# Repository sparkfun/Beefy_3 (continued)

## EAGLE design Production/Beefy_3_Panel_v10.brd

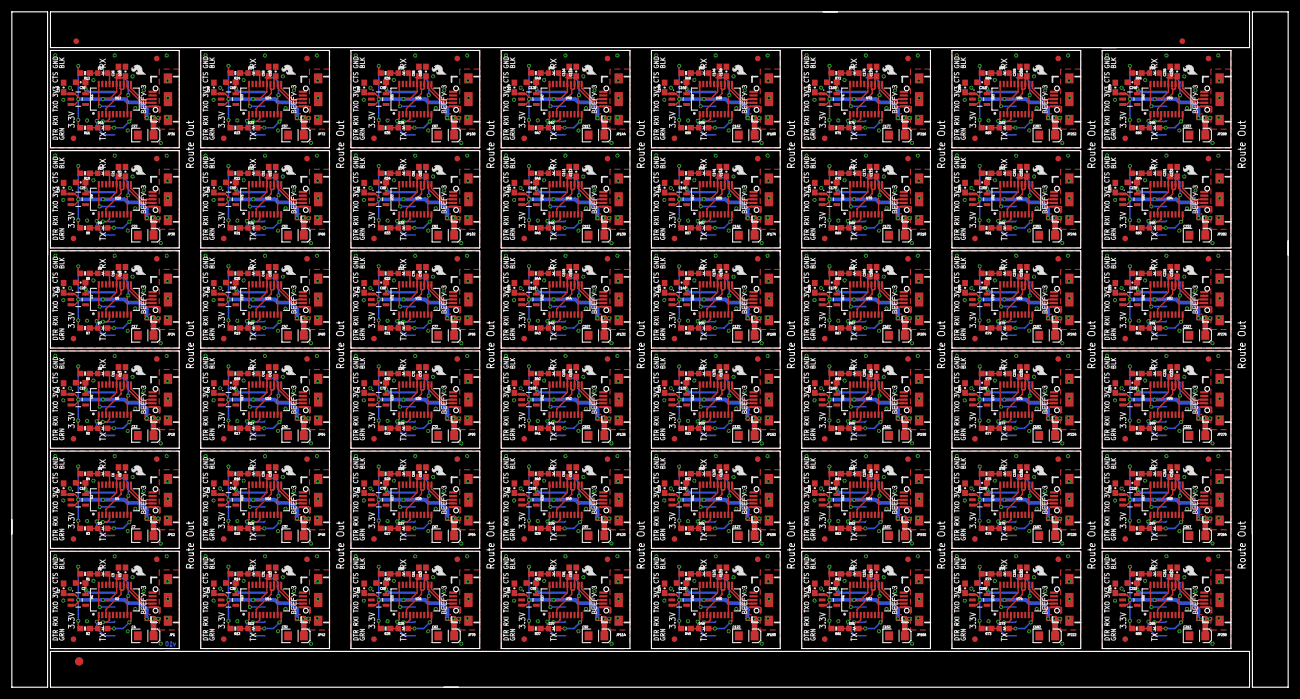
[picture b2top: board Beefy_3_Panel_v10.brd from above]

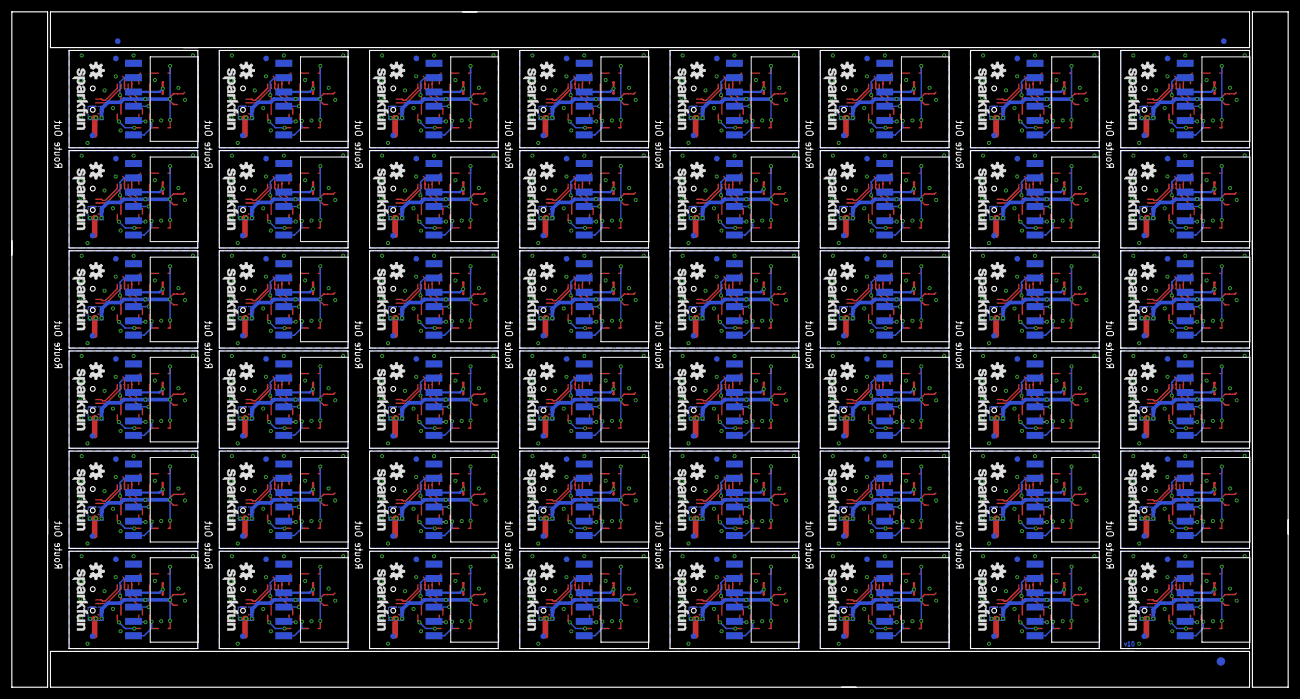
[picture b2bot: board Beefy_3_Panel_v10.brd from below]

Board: 2 copper layers, 226.6 x 119.9 mm, 966 parts (243 on the bottom side), 720 nets.

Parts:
C1, C2, C9, C10, C14, C15, C19, C20, C24, C25, C29, C30, C34, C35, C39, C40, C44, C45, C49, C50, C54, C55, C59, C60, C64, C65, C69, C70, C74, C75, C79, C80, C84, C85, C89, C90, C94, C95, C99, C100, C104, C105, C109, C110, C114, C115, C119, C120, C124, C125, C129, C130, C134, C135, C139, C140, C144, C145, C149, C150, C154, C155, C159, C160, C164, C165, C169, C170, C174, C175, C179, C180, C184, C185, C189, C190, C194, C195, C199, C200, C204, C205, C209, C210, C214, C215, C219, C220, C224, C225, C229, C230, C234, C235, C239, C240: 1.0uF; 0603-CAP
C3, C5, C6, C8, C11, C13, C16, C18, C21, C23, C26, C28, C31, C33, C36, C38, C41, C43, C46, C48, C51, C53, C56, C58, C61, C63, C66, C68, C71, C73, C76, C78, C81, C83, C86, C88, C91, C93, C96, C98, C101, C103, C106, C108, C111, C113, C116, C118, C121, C123, C126, C128, C131, C133, C136, C138, C141, C143, C146, C148, C151, C153, C156, C158, C161, C163, C166, C168, C171, C173, C176, C178, C181, C183, C186, C188, C191, C193, C196, C198, C201, C203, C206, C208, C211, C213, C216, C218, C221, C223, C226, C228, C231, C233, C236, C238: 0.1uF; 0603-CAP
C4, C7, C12, C17, C22, C27, C32, C37, C42, C47, C52, C57, C62, C67, C72, C77, C82, C87, C92, C97, C102, C107, C112, C117, C122, C127, C132, C137, C142, C147, C152, C157, C162, C167, C172, C177, C182, C187, C192, C197, C202, C207, C212, C217, C222, C227, C232, C237: 10uF; EIA3216
D1, D4, D6, D8, D10, D12, D14, D16, D18, D20, D22, D24, D26, D28, D30, D32, D34, D36, D38, D40, D42, D44, D46, D48, D50, D52, D54, D56, D58, D60, D62, D64, D66, D68, D70, D72, D74, D76, D78, D80, D82, D84, D86, D88, D90, D92, D94, D96: GREEN; LED-0603
D2, D3, D5, D7, D9, D11, D13, D15, D17, D19, D21, D23, D25, D27, D29, D31, D33, D35, D37, D39, D41, D43, D45, D47, D49, D51, D53, D55, D57, D59, D61, D63, D65, D67, D69, D71, D73, D75, D77, D79, D81, D83, D85, D87, D89, D91, D93, D95: RED; LED-0603
E$1, E$2: FIDUCIAL-1.5X3
E$3, E$4, E$7, E$8: FIDUCIAL-1X2
JP1, JP12, JP18, JP24, JP30, JP36, JP42, JP48, JP54, JP60, JP66, JP72, JP78, JP84, JP90, JP96, JP102, JP108, JP114, JP120, JP126, JP132, JP138, JP144, JP150, JP156, JP162, JP168, JP174, JP180, JP186, JP192, JP198, JP204, JP210, JP216, JP222, JP228, JP234, JP240, JP246, JP252, JP258, JP264, JP270, JP276, JP282, JP288: USB-B-MICRO-SMD_V03
JP2, JP7, JP13, JP19, JP25, JP31, JP37, JP43, JP49, JP55, JP61, JP67, JP73, JP79, JP85, JP91, JP97, JP103, JP109, JP115, JP121, JP127, JP133, JP139, JP145, JP151, JP157, JP163, JP169, JP175, JP181, JP187, JP193, JP199, JP205, JP211, JP217, JP223, JP229, JP235, JP241, JP247, JP253, JP259, JP265, JP271, JP277, JP283: 1X06-SMD-FEMALE-V2
JP3, JP4, JP5, JP6, JP8, JP9, JP10, JP11, JP14, JP15, JP16, JP17, JP20, JP21, JP22, JP23, JP26, JP27, JP28, JP29, JP32, JP33, JP34, JP35, JP38, JP39, JP40, JP41, JP44, JP45, JP46, JP47, JP50, JP51, JP52, JP53, JP56, JP57, JP58, JP59, JP62, JP63, JP64, JP65, JP68, JP69, JP70, JP71, JP74, JP75, JP76, JP77, JP80, JP81, JP82, JP83, JP86, JP87, JP88, JP89, JP92, JP93, JP94, JP95, JP98, JP99, JP100, JP101, JP104, JP105, JP106, JP107, JP110, JP111, JP112, JP113, JP116, JP117, JP118, JP119, JP122, JP123, JP124, JP125, JP128, JP129, JP130, JP131, JP134, JP135, JP136, JP137, JP140, JP141, JP142, JP143, JP146, JP147, JP148, JP149, JP152, JP153, JP154, JP155, JP158, JP159, JP160, JP161, JP164, JP165, JP166, JP167, JP170, JP171, JP172, JP173, JP176, JP177, JP178, JP179, JP182, JP183, JP184, JP185, JP188, JP189, JP190, JP191, JP194, JP195, JP196, JP197, JP200, JP201, JP202, JP203, JP206, JP207, JP208, JP209, JP212, JP213, JP214, JP215, JP218, JP219, JP220, JP221, JP224, JP225, JP226, JP227, JP230, JP231, JP232, JP233, JP236, JP237, JP238, JP239, JP242, JP243, JP244, JP245, JP248, JP249, JP250, JP251, JP254, JP255, JP256, JP257, JP260, JP261, JP262, JP263, JP266, JP267, JP268, JP269, JP272, JP273, JP274, JP275, JP278, JP279, JP280, JP281, JP284, JP285, JP286, JP287: FIDUCIAL1X2; FIDUCIAL-1X2
LOGO1, LOGO5, LOGO8, LOGO11, LOGO14, LOGO17, LOGO20, LOGO23, LOGO26, LOGO29, LOGO32, LOGO35, LOGO38, LOGO41, LOGO44, LOGO47, LOGO50, LOGO53, LOGO56, LOGO59, LOGO62, LOGO65, LOGO68, LOGO71, LOGO74, LOGO77, LOGO80, LOGO83, LOGO86, LOGO89, LOGO92, LOGO95, LOGO98, LOGO101, LOGO104, LOGO107, LOGO110, LOGO113, LOGO116, LOGO119, LOGO122, LOGO125, LOGO128, LOGO131, LOGO134, LOGO137, LOGO140, LOGO143: OSHW-LOGOS; OSHW-LOGO-S
LOGO2, LOGO4, LOGO7, LOGO10, LOGO13, LOGO16, LOGO19, LOGO22, LOGO25, LOGO28, LOGO31, LOGO34, LOGO37, LOGO40, LOGO43, LOGO46, LOGO49, LOGO52, LOGO55, LOGO58, LOGO61, LOGO64, LOGO67, LOGO70, LOGO73, LOGO76, LOGO79, LOGO82, LOGO85, LOGO88, LOGO91, LOGO94, LOGO97, LOGO100, LOGO103, LOGO106, LOGO109, LOGO112, LOGO115, LOGO118, LOGO121, LOGO124, LOGO127, LOGO130, LOGO133, LOGO136, LOGO139, LOGO142: SFE_LOGO_NAME.1_INCH; SFE_LOGO_NAME_.1
LOGO3, LOGO6, LOGO9, LOGO12, LOGO15, LOGO18, LOGO21, LOGO24, LOGO27, LOGO30, LOGO33, LOGO36, LOGO39, LOGO42, LOGO45, LOGO48, LOGO51, LOGO54, LOGO57, LOGO60, LOGO63, LOGO66, LOGO69, LOGO72, LOGO75, LOGO78, LOGO81, LOGO84, LOGO87, LOGO90, LOGO93, LOGO96, LOGO99, LOGO102, LOGO105, LOGO108, LOGO111, LOGO114, LOGO117, LOGO120, LOGO123, LOGO126, LOGO129, LOGO132, LOGO135, LOGO138, LOGO141, LOGO144: SFE_LOGO_FLAME.1_INCH; SFE_LOGO_FLAME_.1
R1, R2, R3, R4, R5, R6, R7, R8, R9, R10, R11, R12, R13, R14, R15, R16, R17, R18, R19, R20, R21, R22, R23, R24, R25, R26, R27, R28, R29, R30, R31, R32, R33, R34, R35, R36, R37, R38, R39, R40, R41, R42, R43, R44, R45, R46, R47, R48, R49, R50, R51, R52, R53, R54, R55, R56, R57, R58, R59, R60, R61, R62, R63, R64, R65, R66, R67, R68, R69, R70, R71, R72, R73, R74, R75, R76, R77, R78, R79, R80, R81, R82, R83, R84, R85, R86, R87, R88, R89, R90, R91, R92, R93, R94, R95, R96: 1K; 0603-RES
U1, U3, U5, U7, U9, U11, U13, U15, U17, U19, U21, U23, U25, U27, U29, U31, U33, U35, U37, U39, U41, U43, U45, U47, U49, U51, U53, U55, U57, U59, U61, U63, U65, U67, U69, U71, U73, U75, U77, U79, U81, U83, U85, U87, U89, U91, U93, U95: 3.3V; SOT23-5
U2, U4, U6, U8, U10, U12, U14, U16, U18, U20, U22, U24, U26, U28, U30, U32, U34, U36, U38, U40, U42, U44, U46, U48, U50, U52, U54, U56, U58, U60, U62, U64, U66, U68, U70, U72, U74, U76, U78, U80, U82, U84, U86, U88, U90, U92, U94, U96: FTS31XS-U; SSOP20_L

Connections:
3V1: C10.1, JP7.3, U3.5
3V2: C15.1, JP13.3, U5.5
3V3: C2.1, JP2.3, U1.5
3V3LC: C5.1, U2.3, U2.13, U2.14
3V3LC1: C8.1, U4.3, U4.13, U4.14
3V3LC2: C13.1, U6.3, U6.13, U6.14
3V3LC3: C18.1, U8.3, U8.13, U8.14
3V3LC4: C23.1, U10.3, U10.13, U10.14
3V3LC5: C28.1, U12.3, U12.13, U12.14
3V3LC6: C33.1, U14.3, U14.13, U14.14
3V3LC7: C38.1, U16.3, U16.13, U16.14
3V3LC8: C43.1, U18.3, U18.13, U18.14
3V3LC9: C48.1, U20.3, U20.13, U20.14
3V3LC10: C53.1, U22.3, U22.13, U22.14
3V3LC11: C58.1, U24.3, U24.13, U24.14
3V3LC12: C63.1, U26.3, U26.13, U26.14
3V3LC13: C68.1, U28.3, U28.13, U28.14
3V3LC14: C73.1, U30.3, U30.13, U30.14
3V3LC15: C78.1, U32.3, U32.13, U32.14
3V3LC16: C83.1, U34.3, U34.13, U34.14
3V3LC17: C88.1, U36.3, U36.13, U36.14
3V3LC18: C93.1, U38.3, U38.13, U38.14
3V3LC19: C98.1, U40.3, U40.13, U40.14
3V3LC20: C103.1, U42.3, U42.13, U42.14
3V3LC21: C108.1, U44.3, U44.13, U44.14
3V3LC22: C113.1, U46.3, U46.13, U46.14
3V3LC23: C118.1, U48.3, U48.13, U48.14
3V3LC24: C123.1, U50.3, U50.13, U50.14
3V3LC25: C128.1, U52.3, U52.13, U52.14
3V3LC26: C133.1, U54.3, U54.13, U54.14
3V3LC27: C138.1, U56.3, U56.13, U56.14
3V3LC28: C143.1, U58.3, U58.13, U58.14
3V3LC29: C148.1, U60.3, U60.13, U60.14
3V3LC30: C153.1, U62.3, U62.13, U62.14
3V3LC31: C158.1, U64.3, U64.13, U64.14
3V3LC32: C163.1, U66.3, U66.13, U66.14
3V3LC33: C168.1, U68.3, U68.13, U68.14
3V3LC34: C173.1, U70.3, U70.13, U70.14
3V3LC35: C178.1, U72.3, U72.13, U72.14
3V3LC36: C183.1, U74.3, U74.13, U74.14
3V3LC37: C188.1, U76.3, U76.13, U76.14
3V3LC38: C193.1, U78.3, U78.13, U78.14
3V3LC39: C198.1, U80.3, U80.13, U80.14
3V3LC40: C203.1, U82.3, U82.13, U82.14
3V3LC41: C208.1, U84.3, U84.13, U84.14
3V3LC42: C213.1, U86.3, U86.13, U86.14
3V3LC43: C218.1, U88.3, U88.13, U88.14
3V3LC44: C223.1, U90.3, U90.13, U90.14
3V3LC45: C228.1, U92.3, U92.13, U92.14
3V3LC46: C233.1, U94.3, U94.13, U94.14
3V3LC47: C238.1, U96.3, U96.13, U96.14
3V4: C20.1, JP19.3, U7.5
3V5: C25.1, JP25.3, U9.5
3V6: C30.1, JP31.3, U11.5
3V7: C35.1, JP37.3, U13.5
3V8: C40.1, JP43.3, U15.5
3V9: C45.1, JP49.3, U17.5
3V10: C50.1, JP55.3, U19.5
3V11: C55.1, JP61.3, U21.5
3V12: C60.1, JP67.3, U23.5
3V13: C65.1, JP73.3, U25.5
3V14: C70.1, JP79.3, U27.5
3V15: C75.1, JP85.3, U29.5
3V16: C80.1, JP91.3, U31.5
3V17: C85.1, JP97.3, U33.5
3V18: C90.1, JP103.3, U35.5
3V19: C95.1, JP109.3, U37.5
3V20: C100.1, JP115.3, U39.5
3V21: C105.1, JP121.3, U41.5
3V22: C110.1, JP127.3, U43.5
3V23: C115.1, JP133.3, U45.5
3V24: C120.1, JP139.3, U47.5
3V25: C125.1, JP145.3, U49.5
3V26: C130.1, JP151.3, U51.5
3V27: C135.1, JP157.3, U53.5
3V28: C140.1, JP163.3, U55.5
3V29: C145.1, JP169.3, U57.5
3V30: C150.1, JP175.3, U59.5
3V31: C155.1, JP181.3, U61.5
3V32: C160.1, JP187.3, U63.5
3V33: C165.1, JP193.3, U65.5
3V34: C170.1, JP199.3, U67.5
3V35: C175.1, JP205.3, U69.5
3V36: C180.1, JP211.3, U71.5
3V37: C185.1, JP217.3, U73.5
3V38: C190.1, JP223.3, U75.5
3V39: C195.1, JP229.3, U77.5
3V40: C200.1, JP235.3, U79.5
3V41: C205.1, JP241.3, U81.5
3V42: C210.1, JP247.3, U83.5
3V43: C215.1, JP253.3, U85.5
3V44: C220.1, JP259.3, U87.5
3V45: C225.1, JP265.3, U89.5
3V46: C230.1, JP271.3, U91.5
3V47: C235.1, JP277.3, U93.5
3V48: C240.1, JP283.3, U95.5
5V: C1.1, C3.1, C4.A, JP1.VBUS1, R1.2, R2.2, U1.1, U1.3, U2.15
5V1: C6.1, C7.A, C9.1, JP12.VBUS1, R3.2, R4.2, U3.1, U3.3, U4.15
5V2: C11.1, C12.A, C14.1, JP18.VBUS1, R5.2, R6.2, U5.1, U5.3, U6.15
5V3: C16.1, C17.A, C19.1, JP24.VBUS1, R7.2, R8.2, U7.1, U7.3, U8.15
5V4: C21.1, C22.A, C24.1, JP30.VBUS1, R9.2, R10.2, U9.1, U9.3, U10.15
5V5: C26.1, C27.A, C29.1, JP36.VBUS1, R11.2, R12.2, U11.1, U11.3, U12.15
5V6: C31.1, C32.A, C34.1, JP42.VBUS1, R13.2, R14.2, U13.1, U13.3, U14.15
5V7: C36.1, C37.A, C39.1, JP48.VBUS1, R15.2, R16.2, U15.1, U15.3, U16.15
5V8: C41.1, C42.A, C44.1, JP54.VBUS1, R17.2, R18.2, U17.1, U17.3, U18.15
5V9: C46.1, C47.A, C49.1, JP60.VBUS1, R19.2, R20.2, U19.1, U19.3, U20.15
5V10: C51.1, C52.A, C54.1, JP66.VBUS1, R21.2, R22.2, U21.1, U21.3, U22.15
5V11: C56.1, C57.A, C59.1, JP72.VBUS1, R23.2, R24.2, U23.1, U23.3, U24.15
5V12: C61.1, C62.A, C64.1, JP78.VBUS1, R25.2, R26.2, U25.1, U25.3, U26.15
5V13: C66.1, C67.A, C69.1, JP84.VBUS1, R27.2, R28.2, U27.1, U27.3, U28.15
5V14: C71.1, C72.A, C74.1, JP90.VBUS1, R29.2, R30.2, U29.1, U29.3, U30.15
5V15: C76.1, C77.A, C79.1, JP96.VBUS1, R31.2, R32.2, U31.1, U31.3, U32.15
5V16: C81.1, C82.A, C84.1, JP102.VBUS1, R33.2, R34.2, U33.1, U33.3, U34.15
5V17: C86.1, C87.A, C89.1, JP108.VBUS1, R35.2, R36.2, U35.1, U35.3, U36.15
5V18: C91.1, C92.A, C94.1, JP114.VBUS1, R37.2, R38.2, U37.1, U37.3, U38.15
5V19: C96.1, C97.A, C99.1, JP120.VBUS1, R39.2, R40.2, U39.1, U39.3, U40.15
5V20: C101.1, C102.A, C104.1, JP126.VBUS1, R41.2, R42.2, U41.1, U41.3, U42.15
5V21: C106.1, C107.A, C109.1, JP132.VBUS1, R43.2, R44.2, U43.1, U43.3, U44.15
5V22: C111.1, C112.A, C114.1, JP138.VBUS1, R45.2, R46.2, U45.1, U45.3, U46.15
5V23: C116.1, C117.A, C119.1, JP144.VBUS1, R47.2, R48.2, U47.1, U47.3, U48.15
5V24: C121.1, C122.A, C124.1, JP150.VBUS1, R49.2, R50.2, U49.1, U49.3, U50.15
5V25: C126.1, C127.A, C129.1, JP156.VBUS1, R51.2, R52.2, U51.1, U51.3, U52.15
5V26: C131.1, C132.A, C134.1, JP162.VBUS1, R53.2, R54.2, U53.1, U53.3, U54.15
5V27: C136.1, C137.A, C139.1, JP168.VBUS1, R55.2, R56.2, U55.1, U55.3, U56.15
5V28: C141.1, C142.A, C144.1, JP174.VBUS1, R57.2, R58.2, U57.1, U57.3, U58.15
5V29: C146.1, C147.A, C149.1, JP180.VBUS1, R59.2, R60.2, U59.1, U59.3, U60.15
5V30: C151.1, C152.A, C154.1, JP186.VBUS1, R61.2, R62.2, U61.1, U61.3, U62.15
5V31: C156.1, C157.A, C159.1, JP192.VBUS1, R63.2, R64.2, U63.1, U63.3, U64.15
5V32: C161.1, C162.A, C164.1, JP198.VBUS1, R65.2, R66.2, U65.1, U65.3, U66.15
5V33: C166.1, C167.A, C169.1, JP204.VBUS1, R67.2, R68.2, U67.1, U67.3, U68.15
5V34: C171.1, C172.A, C174.1, JP210.VBUS1, R69.2, R70.2, U69.1, U69.3, U70.15
5V35: C176.1, C177.A, C179.1, JP216.VBUS1, R71.2, R72.2, U71.1, U71.3, U72.15
5V36: C181.1, C182.A, C184.1, JP222.VBUS1, R73.2, R74.2, U73.1, U73.3, U74.15
5V37: C186.1, C187.A, C189.1, JP228.VBUS1, R75.2, R76.2, U75.1, U75.3, U76.15
5V38: C191.1, C192.A, C194.1, JP234.VBUS1, R77.2, R78.2, U77.1, U77.3, U78.15
5V39: C196.1, C197.A, C199.1, JP240.VBUS1, R79.2, R80.2, U79.1, U79.3, U80.15
5V40: C201.1, C202.A, C204.1, JP246.VBUS1, R81.2, R82.2, U81.1, U81.3, U82.15
5V41: C206.1, C207.A, C209.1, JP252.VBUS1, R83.2, R84.2, U83.1, U83.3, U84.15
5V42: C211.1, C212.A, C214.1, JP258.VBUS1, R85.2, R86.2, U85.1, U85.3, U86.15
5V43: C216.1, C217.A, C219.1, JP264.VBUS1, R87.2, R88.2, U87.1, U87.3, U88.15
5V44: C221.1, C222.A, C224.1, JP270.VBUS1, R89.2, R90.2, U89.1, U89.3, U90.15
5V45: C226.1, C227.A, C229.1, JP276.VBUS1, R91.2, R92.2, U91.1, U91.3, U92.15
5V46: C231.1, C232.A, C234.1, JP282.VBUS1, R93.2, R94.2, U93.1, U93.3, U94.15
5V47: C236.1, C237.A, C239.1, JP288.VBUS1, R95.2, R96.2, U95.1, U95.3, U96.15
!CTS: JP2.2, U2.9
!CTS1: JP7.2, U4.9
!CTS2: JP13.2, U6.9
!CTS3: JP19.2, U8.9
!CTS4: JP25.2, U10.9
!CTS5: JP31.2, U12.9
!CTS6: JP37.2, U14.9
!CTS7: JP43.2, U16.9
!CTS8: JP49.2, U18.9
!CTS9: JP55.2, U20.9
!CTS10: JP61.2, U22.9
!CTS11: JP67.2, U24.9
!CTS12: JP73.2, U26.9
!CTS13: JP79.2, U28.9
!CTS14: JP85.2, U30.9
!CTS15: JP91.2, U32.9
!CTS16: JP97.2, U34.9
!CTS17: JP103.2, U36.9
!CTS18: JP109.2, U38.9
!CTS19: JP115.2, U40.9
!CTS20: JP121.2, U42.9
!CTS21: JP127.2, U44.9
!CTS22: JP133.2, U46.9
!CTS23: JP139.2, U48.9
!CTS24: JP145.2, U50.9
!CTS25: JP151.2, U52.9
!CTS26: JP157.2, U54.9
!CTS27: JP163.2, U56.9
!CTS28: JP169.2, U58.9
!CTS29: JP175.2, U60.9
!CTS30: JP181.2, U62.9
!CTS31: JP187.2, U64.9
!CTS32: JP193.2, U66.9
!CTS33: JP199.2, U68.9
!CTS34: JP205.2, U70.9
!CTS35: JP211.2, U72.9
!CTS36: JP217.2, U74.9
!CTS37: JP223.2, U76.9
!CTS38: JP229.2, U78.9
!CTS39: JP235.2, U80.9
!CTS40: JP241.2, U82.9
!CTS41: JP247.2, U84.9
!CTS42: JP253.2, U86.9
!CTS43: JP259.2, U88.9
!CTS44: JP265.2, U90.9
!CTS45: JP271.2, U92.9
!CTS46: JP277.2, U94.9
!CTS47: JP283.2, U96.9
!DTR: JP2.6, U2.1
!DTR1: JP7.6, U4.1
!DTR2: JP13.6, U6.1
!DTR3: JP19.6, U8.1
!DTR4: JP25.6, U10.1
!DTR5: JP31.6, U12.1
!DTR6: JP37.6, U14.1
!DTR7: JP43.6, U16.1
!DTR8: JP49.6, U18.1
!DTR9: JP55.6, U20.1
!DTR10: JP61.6, U22.1
!DTR11: JP67.6, U24.1
!DTR12: JP73.6, U26.1
!DTR13: JP79.6, U28.1
!DTR14: JP85.6, U30.1
!DTR15: JP91.6, U32.1
!DTR16: JP97.6, U34.1
!DTR17: JP103.6, U36.1
!DTR18: JP109.6, U38.1
!DTR19: JP115.6, U40.1
!DTR20: JP121.6, U42.1
!DTR21: JP127.6, U44.1
!DTR22: JP133.6, U46.1
!DTR23: JP139.6, U48.1
!DTR24: JP145.6, U50.1
!DTR25: JP151.6, U52.1
!DTR26: JP157.6, U54.1
!DTR27: JP163.6, U56.1
!DTR28: JP169.6, U58.1
!DTR29: JP175.6, U60.1
!DTR30: JP181.6, U62.1
!DTR31: JP187.6, U64.1
!DTR32: JP193.6, U66.1
!DTR33: JP199.6, U68.1
!DTR34: JP205.6, U70.1
!DTR35: JP211.6, U72.1
!DTR36: JP217.6, U74.1
!DTR37: JP223.6, U76.1
!DTR38: JP229.6, U78.1
!DTR39: JP235.6, U80.1
!DTR40: JP241.6, U82.1
!DTR41: JP247.6, U84.1
!DTR42: JP253.6, U86.1
!DTR43: JP259.6, U88.1
!DTR44: JP265.6, U90.1
!DTR45: JP271.6, U92.1
!DTR46: JP277.6, U94.1
!DTR47: JP283.6, U96.1
GND: C1.2, C2.2, C3.2, C4.C, C5.2, JP1.GND1, JP2.1, U1.2, U2.6, U2.16
GND1: C6.2, C7.C, C8.2, C9.2, C10.2, JP7.1, JP12.GND1, U3.2, U4.6, U4.16
GND2: C11.2, C12.C, C13.2, C14.2, C15.2, JP13.1, JP18.GND1, U5.2, U6.6, U6.16
GND3: C16.2, C17.C, C18.2, C19.2, C20.2, JP19.1, JP24.GND1, U7.2, U8.6, U8.16
GND4: C21.2, C22.C, C23.2, C24.2, C25.2, JP25.1, JP30.GND1, U9.2, U10.6, U10.16
GND5: C26.2, C27.C, C28.2, C29.2, C30.2, JP31.1, JP36.GND1, U11.2, U12.6, U12.16
GND6: C31.2, C32.C, C33.2, C34.2, C35.2, JP37.1, JP42.GND1, U13.2, U14.6, U14.16
GND7: C36.2, C37.C, C38.2, C39.2, C40.2, JP43.1, JP48.GND1, U15.2, U16.6, U16.16
GND8: C41.2, C42.C, C43.2, C44.2, C45.2, JP49.1, JP54.GND1, U17.2, U18.6, U18.16
GND9: C46.2, C47.C, C48.2, C49.2, C50.2, JP55.1, JP60.GND1, U19.2, U20.6, U20.16
GND10: C51.2, C52.C, C53.2, C54.2, C55.2, JP61.1, JP66.GND1, U21.2, U22.6, U22.16
GND11: C56.2, C57.C, C58.2, C59.2, C60.2, JP67.1, JP72.GND1, U23.2, U24.6, U24.16
GND12: C61.2, C62.C, C63.2, C64.2, C65.2, JP73.1, JP78.GND1, U25.2, U26.6, U26.16
GND13: C66.2, C67.C, C68.2, C69.2, C70.2, JP79.1, JP84.GND1, U27.2, U28.6, U28.16
GND14: C71.2, C72.C, C73.2, C74.2, C75.2, JP85.1, JP90.GND1, U29.2, U30.6, U30.16
GND15: C76.2, C77.C, C78.2, C79.2, C80.2, JP91.1, JP96.GND1, U31.2, U32.6, U32.16
GND16: C81.2, C82.C, C83.2, C84.2, C85.2, JP97.1, JP102.GND1, U33.2, U34.6, U34.16
GND17: C86.2, C87.C, C88.2, C89.2, C90.2, JP103.1, JP108.GND1, U35.2, U36.6, U36.16
GND18: C91.2, C92.C, C93.2, C94.2, C95.2, JP109.1, JP114.GND1, U37.2, U38.6, U38.16
GND19: C96.2, C97.C, C98.2, C99.2, C100.2, JP115.1, JP120.GND1, U39.2, U40.6, U40.16
GND20: C101.2, C102.C, C103.2, C104.2, C105.2, JP121.1, JP126.GND1, U41.2, U42.6, U42.16
GND21: C106.2, C107.C, C108.2, C109.2, C110.2, JP127.1, JP132.GND1, U43.2, U44.6, U44.16
GND22: C111.2, C112.C, C113.2, C114.2, C115.2, JP133.1, JP138.GND1, U45.2, U46.6, U46.16
GND23: C116.2, C117.C, C118.2, C119.2, C120.2, JP139.1, JP144.GND1, U47.2, U48.6, U48.16
GND24: C121.2, C122.C, C123.2, C124.2, C125.2, JP145.1, JP150.GND1, U49.2, U50.6, U50.16
GND25: C126.2, C127.C, C128.2, C129.2, C130.2, JP151.1, JP156.GND1, U51.2, U52.6, U52.16
GND26: C131.2, C132.C, C133.2, C134.2, C135.2, JP157.1, JP162.GND1, U53.2, U54.6, U54.16
GND27: C136.2, C137.C, C138.2, C139.2, C140.2, JP163.1, JP168.GND1, U55.2, U56.6, U56.16
GND28: C141.2, C142.C, C143.2, C144.2, C145.2, JP169.1, JP174.GND1, U57.2, U58.6, U58.16
GND29: C146.2, C147.C, C148.2, C149.2, C150.2, JP175.1, JP180.GND1, U59.2, U60.6, U60.16
GND30: C151.2, C152.C, C153.2, C154.2, C155.2, JP181.1, JP186.GND1, U61.2, U62.6, U62.16
GND31: C156.2, C157.C, C158.2, C159.2, C160.2, JP187.1, JP192.GND1, U63.2, U64.6, U64.16
GND32: C161.2, C162.C, C163.2, C164.2, C165.2, JP193.1, JP198.GND1, U65.2, U66.6, U66.16
GND33: C166.2, C167.C, C168.2, C169.2, C170.2, JP199.1, JP204.GND1, U67.2, U68.6, U68.16
GND34: C171.2, C172.C, C173.2, C174.2, C175.2, JP205.1, JP210.GND1, U69.2, U70.6, U70.16
GND35: C176.2, C177.C, C178.2, C179.2, C180.2, JP211.1, JP216.GND1, U71.2, U72.6, U72.16
GND36: C181.2, C182.C, C183.2, C184.2, C185.2, JP217.1, JP222.GND1, U73.2, U74.6, U74.16
GND37: C186.2, C187.C, C188.2, C189.2, C190.2, JP223.1, JP228.GND1, U75.2, U76.6, U76.16
GND38: C191.2, C192.C, C193.2, C194.2, C195.2, JP229.1, JP234.GND1, U77.2, U78.6, U78.16
GND39: C196.2, C197.C, C198.2, C199.2, C200.2, JP235.1, JP240.GND1, U79.2, U80.6, U80.16
GND40: C201.2, C202.C, C203.2, C204.2, C205.2, JP241.1, JP246.GND1, U81.2, U82.6, U82.16
GND41: C206.2, C207.C, C208.2, C209.2, C210.2, JP247.1, JP252.GND1, U83.2, U84.6, U84.16
GND42: C211.2, C212.C, C213.2, C214.2, C215.2, JP253.1, JP258.GND1, U85.2, U86.6, U86.16
GND43: C216.2, C217.C, C218.2, C219.2, C220.2, JP259.1, JP264.GND1, U87.2, U88.6, U88.16
GND44: C221.2, C222.C, C223.2, C224.2, C225.2, JP265.1, JP270.GND1, U89.2, U90.6, U90.16
GND45: C226.2, C227.C, C228.2, C229.2, C230.2, JP271.1, JP276.GND1, U91.2, U92.6, U92.16
GND46: C231.2, C232.C, C233.2, C234.2, C235.2, JP277.1, JP282.GND1, U93.2, U94.6, U94.16
GND47: C236.2, C237.C, C238.2, C239.2, C240.2, JP283.1, JP288.GND1, U95.2, U96.6, U96.16
unnamed: D2.A, R2.1
unnamed: D1.A, R1.1
unnamed: D3.A, R3.1
unnamed: D4.A, R4.1
unnamed: D5.A, R5.1
unnamed: D6.A, R6.1
unnamed: D7.A, R7.1
unnamed: D8.A, R8.1
unnamed: D9.A, R9.1
unnamed: D10.A, R10.1
unnamed: D11.A, R11.1
unnamed: D12.A, R12.1
unnamed: D13.A, R13.1
unnamed: D14.A, R14.1
unnamed: D15.A, R15.1
unnamed: D16.A, R16.1
unnamed: D17.A, R17.1
unnamed: D18.A, R18.1
unnamed: D19.A, R19.1
unnamed: D20.A, R20.1
unnamed: D21.A, R21.1
unnamed: D22.A, R22.1
unnamed: D23.A, R23.1
unnamed: D24.A, R24.1
unnamed: D25.A, R25.1
unnamed: D26.A, R26.1
unnamed: D27.A, R27.1
unnamed: D28.A, R28.1
unnamed: D29.A, R29.1
unnamed: D30.A, R30.1
unnamed: D31.A, R31.1
unnamed: D32.A, R32.1
unnamed: D33.A, R33.1
unnamed: D34.A, R34.1
unnamed: D35.A, R35.1
unnamed: D36.A, R36.1
unnamed: D37.A, R37.1
unnamed: D38.A, R38.1
unnamed: D39.A, R39.1
unnamed: D40.A, R40.1
unnamed: D41.A, R41.1
unnamed: D42.A, R42.1
unnamed: D43.A, R43.1
unnamed: D44.A, R44.1
unnamed: D45.A, R45.1
unnamed: D46.A, R46.1
unnamed: D47.A, R47.1
unnamed: D48.A, R48.1
unnamed: D49.A, R49.1
unnamed: D50.A, R50.1
unnamed: D51.A, R51.1
unnamed: D52.A, R52.1
unnamed: D53.A, R53.1
unnamed: D54.A, R54.1
unnamed: D55.A, R55.1
unnamed: D56.A, R56.1
unnamed: D57.A, R57.1
unnamed: D58.A, R58.1
unnamed: D59.A, R59.1
unnamed: D60.A, R60.1
unnamed: D61.A, R61.1
unnamed: D62.A, R62.1
unnamed: D63.A, R63.1
unnamed: D64.A, R64.1
unnamed: D65.A, R65.1
unnamed: D66.A, R66.1
unnamed: D67.A, R67.1
unnamed: D68.A, R68.1
unnamed: D69.A, R69.1
unnamed: D70.A, R70.1
unnamed: D71.A, R71.1
unnamed: D72.A, R72.1
unnamed: D73.A, R73.1
unnamed: D74.A, R74.1
unnamed: D75.A, R75.1
unnamed: D76.A, R76.1
unnamed: D77.A, R77.1
unnamed: D78.A, R78.1
unnamed: D79.A, R79.1
unnamed: D80.A, R80.1
unnamed: D81.A, R81.1
unnamed: D82.A, R82.1
unnamed: D83.A, R83.1
unnamed: D84.A, R84.1
unnamed: D85.A, R85.1
unnamed: D86.A, R86.1
unnamed: D87.A, R87.1
unnamed: D88.A, R88.1
unnamed: D89.A, R89.1
unnamed: D90.A, R90.1
unnamed: D91.A, R91.1
unnamed: D92.A, R92.1
unnamed: D93.A, R93.1
unnamed: D94.A, R94.1
unnamed: D95.A, R95.1
unnamed: D96.A, R96.1
RXI: JP2.5, U2.4
RXI1: JP7.5, U4.4
RXI2: JP13.5, U6.4
RXI3: JP19.5, U8.4
RXI4: JP25.5, U10.4
RXI5: JP31.5, U12.4
RXI6: JP37.5, U14.4
RXI7: JP43.5, U16.4
RXI8: JP49.5, U18.4
RXI9: JP55.5, U20.4
RXI10: JP61.5, U22.4
RXI11: JP67.5, U24.4
RXI12: JP73.5, U26.4
RXI13: JP79.5, U28.4
RXI14: JP85.5, U30.4
RXI15: JP91.5, U32.4
RXI16: JP97.5, U34.4
RXI17: JP103.5, U36.4
RXI18: JP109.5, U38.4
RXI19: JP115.5, U40.4
RXI20: JP121.5, U42.4
RXI21: JP127.5, U44.4
RXI22: JP133.5, U46.4
RXI23: JP139.5, U48.4
RXI24: JP145.5, U50.4
RXI25: JP151.5, U52.4
RXI26: JP157.5, U54.4
RXI27: JP163.5, U56.4
RXI28: JP169.5, U58.4
RXI29: JP175.5, U60.4
RXI30: JP181.5, U62.4
RXI31: JP187.5, U64.4
RXI32: JP193.5, U66.4
RXI33: JP199.5, U68.4
RXI34: JP205.5, U70.4
RXI35: JP211.5, U72.4
RXI36: JP217.5, U74.4
RXI37: JP223.5, U76.4
RXI38: JP229.5, U78.4
RXI39: JP235.5, U80.4
RXI40: JP241.5, U82.4
RXI41: JP247.5, U84.4
RXI42: JP253.5, U86.4
RXI43: JP259.5, U88.4
RXI44: JP265.5, U90.4
RXI45: JP271.5, U92.4
RXI46: JP277.5, U94.4
RXI47: JP283.5, U96.4
RXLED: D1.C, U2.17
RXLED1: D4.C, U4.17
RXLED2: D6.C, U6.17
RXLED3: D8.C, U8.17
RXLED4: D10.C, U10.17
RXLED5: D12.C, U12.17
RXLED6: D14.C, U14.17
RXLED7: D16.C, U16.17
RXLED8: D18.C, U18.17
RXLED9: D20.C, U20.17
RXLED10: D22.C, U22.17
RXLED11: D24.C, U24.17
RXLED12: D26.C, U26.17
RXLED13: D28.C, U28.17
RXLED14: D30.C, U30.17
RXLED15: D32.C, U32.17
RXLED16: D34.C, U34.17
RXLED17: D36.C, U36.17
RXLED18: D38.C, U38.17
RXLED19: D40.C, U40.17
RXLED20: D42.C, U42.17
RXLED21: D44.C, U44.17
RXLED22: D46.C, U46.17
RXLED23: D48.C, U48.17
RXLED24: D50.C, U50.17
RXLED25: D52.C, U52.17
RXLED26: D54.C, U54.17
RXLED27: D56.C, U56.17
RXLED28: D58.C, U58.17
RXLED29: D60.C, U60.17
RXLED30: D62.C, U62.17
RXLED31: D64.C, U64.17
RXLED32: D66.C, U66.17
RXLED33: D68.C, U68.17
RXLED34: D70.C, U70.17
RXLED35: D72.C, U72.17
RXLED36: D74.C, U74.17
RXLED37: D76.C, U76.17
RXLED38: D78.C, U78.17
RXLED39: D80.C, U80.17
RXLED40: D82.C, U82.17
RXLED41: D84.C, U84.17
RXLED42: D86.C, U86.17
RXLED43: D88.C, U88.17
RXLED44: D90.C, U90.17
RXLED45: D92.C, U92.17
RXLED46: D94.C, U94.17
RXLED47: D96.C, U96.17
SHIELD: JP1.SHIELD1, JP1.SHIELD2, JP1.SHIELD3
SHIELD1: JP12.SHIELD1, JP12.SHIELD2, JP12.SHIELD3
SHIELD2: JP18.SHIELD1, JP18.SHIELD2, JP18.SHIELD3
SHIELD3: JP24.SHIELD1, JP24.SHIELD2, JP24.SHIELD3
SHIELD4: JP30.SHIELD1, JP30.SHIELD2, JP30.SHIELD3
SHIELD5: JP36.SHIELD1, JP36.SHIELD2, JP36.SHIELD3
SHIELD6: JP42.SHIELD1, JP42.SHIELD2, JP42.SHIELD3
SHIELD7: JP48.SHIELD1, JP48.SHIELD2, JP48.SHIELD3
SHIELD8: JP54.SHIELD1, JP54.SHIELD2, JP54.SHIELD3
SHIELD9: JP60.SHIELD1, JP60.SHIELD2, JP60.SHIELD3
SHIELD10: JP66.SHIELD1, JP66.SHIELD2, JP66.SHIELD3
SHIELD11: JP72.SHIELD1, JP72.SHIELD2, JP72.SHIELD3
SHIELD12: JP78.SHIELD1, JP78.SHIELD2, JP78.SHIELD3
SHIELD13: JP84.SHIELD1, JP84.SHIELD2, JP84.SHIELD3
SHIELD14: JP90.SHIELD1, JP90.SHIELD2, JP90.SHIELD3
SHIELD15: JP96.SHIELD1, JP96.SHIELD2, JP96.SHIELD3
SHIELD16: JP102.SHIELD1, JP102.SHIELD2, JP102.SHIELD3
SHIELD17: JP108.SHIELD1, JP108.SHIELD2, JP108.SHIELD3
SHIELD18: JP114.SHIELD1, JP114.SHIELD2, JP114.SHIELD3
SHIELD19: JP120.SHIELD1, JP120.SHIELD2, JP120.SHIELD3
SHIELD20: JP126.SHIELD1, JP126.SHIELD2, JP126.SHIELD3
SHIELD21: JP132.SHIELD1, JP132.SHIELD2, JP132.SHIELD3
SHIELD22: JP138.SHIELD1, JP138.SHIELD2, JP138.SHIELD3
SHIELD23: JP144.SHIELD1, JP144.SHIELD2, JP144.SHIELD3
SHIELD24: JP150.SHIELD1, JP150.SHIELD2, JP150.SHIELD3
SHIELD25: JP156.SHIELD1, JP156.SHIELD2, JP156.SHIELD3
SHIELD26: JP162.SHIELD1, JP162.SHIELD2, JP162.SHIELD3
SHIELD27: JP168.SHIELD1, JP168.SHIELD2, JP168.SHIELD3
SHIELD28: JP174.SHIELD1, JP174.SHIELD2, JP174.SHIELD3
SHIELD29: JP180.SHIELD1, JP180.SHIELD2, JP180.SHIELD3
SHIELD30: JP186.SHIELD1, JP186.SHIELD2, JP186.SHIELD3
SHIELD31: JP192.SHIELD1, JP192.SHIELD2, JP192.SHIELD3
SHIELD32: JP198.SHIELD1, JP198.SHIELD2, JP198.SHIELD3
SHIELD33: JP204.SHIELD1, JP204.SHIELD2, JP204.SHIELD3
SHIELD34: JP210.SHIELD1, JP210.SHIELD2, JP210.SHIELD3
SHIELD35: JP216.SHIELD1, JP216.SHIELD2, JP216.SHIELD3
SHIELD36: JP222.SHIELD1, JP222.SHIELD2, JP222.SHIELD3
SHIELD37: JP228.SHIELD1, JP228.SHIELD2, JP228.SHIELD3
SHIELD38: JP234.SHIELD1, JP234.SHIELD2, JP234.SHIELD3
SHIELD39: JP240.SHIELD1, JP240.SHIELD2, JP240.SHIELD3
SHIELD40: JP246.SHIELD1, JP246.SHIELD2, JP246.SHIELD3
SHIELD41: JP252.SHIELD1, JP252.SHIELD2, JP252.SHIELD3
SHIELD42: JP258.SHIELD1, JP258.SHIELD2, JP258.SHIELD3
SHIELD43: JP264.SHIELD1, JP264.SHIELD2, JP264.SHIELD3
SHIELD44: JP270.SHIELD1, JP270.SHIELD2, JP270.SHIELD3
SHIELD45: JP276.SHIELD1, JP276.SHIELD2, JP276.SHIELD3
SHIELD46: JP282.SHIELD1, JP282.SHIELD2, JP282.SHIELD3
SHIELD47: JP288.SHIELD1, JP288.SHIELD2, JP288.SHIELD3
TXLED: D2.C, U2.10
TXLED1: D3.C, U4.10
TXLED2: D5.C, U6.10
TXLED3: D7.C, U8.10
TXLED4: D9.C, U10.10
TXLED5: D11.C, U12.10
TXLED6: D13.C, U14.10
TXLED7: D15.C, U16.10
TXLED8: D17.C, U18.10
TXLED9: D19.C, U20.10
TXLED10: D21.C, U22.10
TXLED11: D23.C, U24.10
TXLED12: D25.C, U26.10
TXLED13: D27.C, U28.10
TXLED14: D29.C, U30.10
TXLED15: D31.C, U32.10
TXLED16: D33.C, U34.10
TXLED17: D35.C, U36.10
TXLED18: D37.C, U38.10
TXLED19: D39.C, U40.10
TXLED20: D41.C, U42.10
TXLED21: D43.C, U44.10
TXLED22: D45.C, U46.10
TXLED23: D47.C, U48.10
TXLED24: D49.C, U50.10
TXLED25: D51.C, U52.10
TXLED26: D53.C, U54.10
TXLED27: D55.C, U56.10
TXLED28: D57.C, U58.10
TXLED29: D59.C, U60.10
TXLED30: D61.C, U62.10
TXLED31: D63.C, U64.10
TXLED32: D65.C, U66.10
TXLED33: D67.C, U68.10
TXLED34: D69.C, U70.10
TXLED35: D71.C, U72.10
TXLED36: D73.C, U74.10
TXLED37: D75.C, U76.10
TXLED38: D77.C, U78.10
TXLED39: D79.C, U80.10
TXLED40: D81.C, U82.10
TXLED41: D83.C, U84.10
TXLED42: D85.C, U86.10
TXLED43: D87.C, U88.10
TXLED44: D89.C, U90.10
TXLED45: D91.C, U92.10
TXLED46: D93.C, U94.10
TXLED47: D95.C, U96.10
TXO: JP2.4, U2.20
TXO1: JP7.4, U4.20
TXO2: JP13.4, U6.20
TXO3: JP19.4, U8.20
TXO4: JP25.4, U10.20
TXO5: JP31.4, U12.20
TXO6: JP37.4, U14.20
TXO7: JP43.4, U16.20
TXO8: JP49.4, U18.20
TXO9: JP55.4, U20.20
TXO10: JP61.4, U22.20
TXO11: JP67.4, U24.20
TXO12: JP73.4, U26.20
TXO13: JP79.4, U28.20
TXO14: JP85.4, U30.20
TXO15: JP91.4, U32.20
TXO16: JP97.4, U34.20
TXO17: JP103.4, U36.20
TXO18: JP109.4, U38.20
TXO19: JP115.4, U40.20
TXO20: JP121.4, U42.20
TXO21: JP127.4, U44.20
TXO22: JP133.4, U46.20
TXO23: JP139.4, U48.20
TXO24: JP145.4, U50.20
TXO25: JP151.4, U52.20
TXO26: JP157.4, U54.20
TXO27: JP163.4, U56.20
TXO28: JP169.4, U58.20
TXO29: JP175.4, U60.20
TXO30: JP181.4, U62.20
TXO31: JP187.4, U64.20
TXO32: JP193.4, U66.20
TXO33: JP199.4, U68.20
TXO34: JP205.4, U70.20
TXO35: JP211.4, U72.20
TXO36: JP217.4, U74.20
TXO37: JP223.4, U76.20
TXO38: JP229.4, U78.20
TXO39: JP235.4, U80.20
TXO40: JP241.4, U82.20
TXO41: JP247.4, U84.20
TXO42: JP253.4, U86.20
TXO43: JP259.4, U88.20
TXO44: JP265.4, U90.20
TXO45: JP271.4, U92.20
TXO46: JP277.4, U94.20
TXO47: JP283.4, U96.20
USB_D+: JP1.D+1, U2.11
USB_D+1: JP12.D+1, U4.11
USB_D+2: JP18.D+1, U6.11
USB_D+3: JP24.D+1, U8.11
USB_D+4: JP30.D+1, U10.11
USB_D+5: JP36.D+1, U12.11
USB_D+6: JP42.D+1, U14.11
USB_D+7: JP48.D+1, U16.11
USB_D+8: JP54.D+1, U18.11
USB_D+9: JP60.D+1, U20.11
USB_D+10: JP66.D+1, U22.11
USB_D+11: JP72.D+1, U24.11
USB_D+12: JP78.D+1, U26.11
USB_D+13: JP84.D+1, U28.11
USB_D+14: JP90.D+1, U30.11
USB_D+15: JP96.D+1, U32.11
USB_D+16: JP102.D+1, U34.11
USB_D+17: JP108.D+1, U36.11
USB_D+18: JP114.D+1, U38.11
USB_D+19: JP120.D+1, U40.11
USB_D+20: JP126.D+1, U42.11
USB_D+21: JP132.D+1, U44.11
USB_D+22: JP138.D+1, U46.11
USB_D+23: JP144.D+1, U48.11
USB_D+24: JP150.D+1, U50.11
USB_D+25: JP156.D+1, U52.11
USB_D+26: JP162.D+1, U54.11
USB_D+27: JP168.D+1, U56.11
USB_D+28: JP174.D+1, U58.11
USB_D+29: JP180.D+1, U60.11
USB_D+30: JP186.D+1, U62.11
USB_D+31: JP192.D+1, U64.11
USB_D+32: JP198.D+1, U66.11
USB_D+33: JP204.D+1, U68.11
USB_D+34: JP210.D+1, U70.11
USB_D+35: JP216.D+1, U72.11
USB_D+36: JP222.D+1, U74.11
USB_D+37: JP228.D+1, U76.11
USB_D+38: JP234.D+1, U78.11
USB_D+39: JP240.D+1, U80.11
USB_D+40: JP246.D+1, U82.11
USB_D+41: JP252.D+1, U84.11
USB_D+42: JP258.D+1, U86.11
USB_D+43: JP264.D+1, U88.11
USB_D+44: JP270.D+1, U90.11
USB_D+45: JP276.D+1, U92.11
USB_D+46: JP282.D+1, U94.11
USB_D+47: JP288.D+1, U96.11
USB_D-: JP1.D-1, U2.12
USB_D-1: JP12.D-1, U4.12
USB_D-2: JP18.D-1, U6.12
USB_D-3: JP24.D-1, U8.12
USB_D-4: JP30.D-1, U10.12
USB_D-5: JP36.D-1, U12.12
USB_D-6: JP42.D-1, U14.12
USB_D-7: JP48.D-1, U16.12
USB_D-8: JP54.D-1, U18.12
USB_D-9: JP60.D-1, U20.12
USB_D-10: JP66.D-1, U22.12
USB_D-11: JP72.D-1, U24.12
USB_D-12: JP78.D-1, U26.12
USB_D-13: JP84.D-1, U28.12
USB_D-14: JP90.D-1, U30.12
USB_D-15: JP96.D-1, U32.12
USB_D-16: JP102.D-1, U34.12
USB_D-17: JP108.D-1, U36.12
USB_D-18: JP114.D-1, U38.12
USB_D-19: JP120.D-1, U40.12
USB_D-20: JP126.D-1, U42.12
USB_D-21: JP132.D-1, U44.12
USB_D-22: JP138.D-1, U46.12
USB_D-23: JP144.D-1, U48.12
USB_D-24: JP150.D-1, U50.12
USB_D-25: JP156.D-1, U52.12
USB_D-26: JP162.D-1, U54.12
USB_D-27: JP168.D-1, U56.12
USB_D-28: JP174.D-1, U58.12
USB_D-29: JP180.D-1, U60.12
USB_D-30: JP186.D-1, U62.12
USB_D-31: JP192.D-1, U64.12
USB_D-32: JP198.D-1, U66.12
USB_D-33: JP204.D-1, U68.12
USB_D-34: JP210.D-1, U70.12
USB_D-35: JP216.D-1, U72.12
USB_D-36: JP222.D-1, U74.12
USB_D-37: JP228.D-1, U76.12
USB_D-38: JP234.D-1, U78.12
USB_D-39: JP240.D-1, U80.12
USB_D-40: JP246.D-1, U82.12
USB_D-41: JP252.D-1, U84.12
USB_D-42: JP258.D-1, U86.12
USB_D-43: JP264.D-1, U88.12
USB_D-44: JP270.D-1, U90.12
USB_D-45: JP276.D-1, U92.12
USB_D-46: JP282.D-1, U94.12
USB_D-47: JP288.D-1, U96.12

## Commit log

2015-10-12 Tweaked README
2015-10-13 Improved high-speed differential routing
2015-10-13 Added PROD_IDs to library parts and updated them
2015-10-19 First pass at using micro B & FT231X
2015-10-21 New layout
2015-10-22 Changed product name font
2015-10-22 Added 15 mil staking vias
2015-10-22 Approved 'errors'
2015-11-25 Updated version number
2015-11-25 Added shield pour
2015-11-30 Added flame logo to top and clarified schematic note
2015-12-10 moved board fids
2015-12-10 created panel v10
2016-01-27 added bottom side panel fiducials
2016-02-18 Changed image to actual part.
2016-02-18 Updated link to this product
2016-02-18 Minor format change
